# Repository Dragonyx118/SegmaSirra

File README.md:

# 🌿 SegmaSirra — Smart Solar Greenhouse

<p align="center">
<b>Un'ecosistema IoT completo per la gestione, l'irrigazione e il monitoraggio remoto di una serra automatizzata e autosufficiente.</b>
</p>

<br />

---

## 📌 Indice
- [Cos'è SegmaSirra?](#-cosè-segmasirra)
- [Galleria Fotografica](#-galleria-fotografica)
- [Architettura del Sistema](#-architettura-del-sistema)
- [Specifiche Hardware](#-specifiche-hardware)
- [Funzionalità nel Dettaglio](#-funzionalità-nel-dettaglio)
- [Struttura della Repository](#-struttura-della-repository)
- [Guida all'Installazione](#-guida-allinstallazione)
- [1. Firmware (ESP32)](#1-firmware-esp32)
- [2. App Android](#2-app-android)
- [Roadmap & Sviluppi Futuri](#-roadmap--sviluppi-futuri)
- [Licenza](#-licenza)

---

## 🍃 Cos'è SegmaSirra?

**SegmaSirra** è una serra domotica completamente **autosufficiente dal punto di vista energetico**, progettata per ottimizzare la crescita delle piante senza richiedere interventi umani continui.
**SegmaSirra** è una serra domotica completamente **autosufficiente**, progettata per ottimizzare la crescita delle piante senza richiedere interventi umani continui.

Grazie al microcontrollore **ESP32-WROOM-32** e all'alimentazione integrata da pannello solare a 12V, il sistema analizza costantemente i parametri ambientali (temperatura, umidità del suolo e dell'aria, luminosità) ed esegue azioni correttive automatiche. Tutto l'ecosistema è interfacciato in tempo reale con un'app Android dedicata tramite connessione Wi-Fi.

🌐 **Sito del Progetto:** [dragonyx118.github.io/SegmaSirra-Web/](https://dragonyx118.github.io/SegmaSirra-Web/)

---

## 📱 App Android (SegmaIpp)

Il controllo e il monitoraggio remoto della serra avvengono tramite un'applicazione Android sviluppata ad hoc e ospitata in una repository dedicata:

👉 **Repository dell'App:** [**Dragonyx118/SegmaIpp**](https://github.com/Dragonyx118/SegmaIpp)

### Caratteristiche dell'App:
* **Dashboard in tempo reale:** Visualizzazione dei dati di temperatura, umidità ambientale, umidità del terreno e luminosità.
* **Controllo remoto manuale:** Attivazione forzata dell'irrigazione, gestione delle luci notturne ed apertura/chiusura del tetto via Wi-Fi.
* **Notifiche ed avvisi:** Monitoraggio dello stato delle cisterne e della batteria.

---

## 📸 Galleria Fotografica
## 📸 Galleria

<div align="center">
<table>
<tr>
 <td align="center" width="50%">
   <br />
   <b></b>
 </td>
 <td align="center" width="50%">
   <br />
   <b></b>
 </td>
</tr>
<tr>
 <td align="center" width="50%">
   <br />
   <b></b>
 </td>
 <td align="center" width="50%">
   <br />
   <b></b>
 </td>
</tr>
</table>
</div>

---

## ⚡ Architettura del Sistema

```text
              +----------------------------------+
              |     Pannello Solare + Reg.      |
              +-----------------+----------------+
                                |
                                v
                      +------------------+
                      | Batteria AGM 12V |
                      +--------+---------+
                                |
                                v
+--------------------------------+--------------------------------+
|                       Modulo ESP32-WROOM-32                      |
|                                                                 |
|  [Sensori Clima & Luce]  --->  Elaborazione Data  --->  [Wi-Fi] |
+-------+------------------------+------------------------+-------+
       |                        |                        |
       v                        v                        v
+---------------+        +---------------+        +---------------+
|   Attuatori   |        | Servomotori   |        |  App Android  |
| 2x Ventole    |        | Apertura      |        | Monitoraggio  |
| 2x Pompe 12V  |        | Tetto         |        |  & Comandi    |
| Luci Notturne |        +---------------+        +---------------+

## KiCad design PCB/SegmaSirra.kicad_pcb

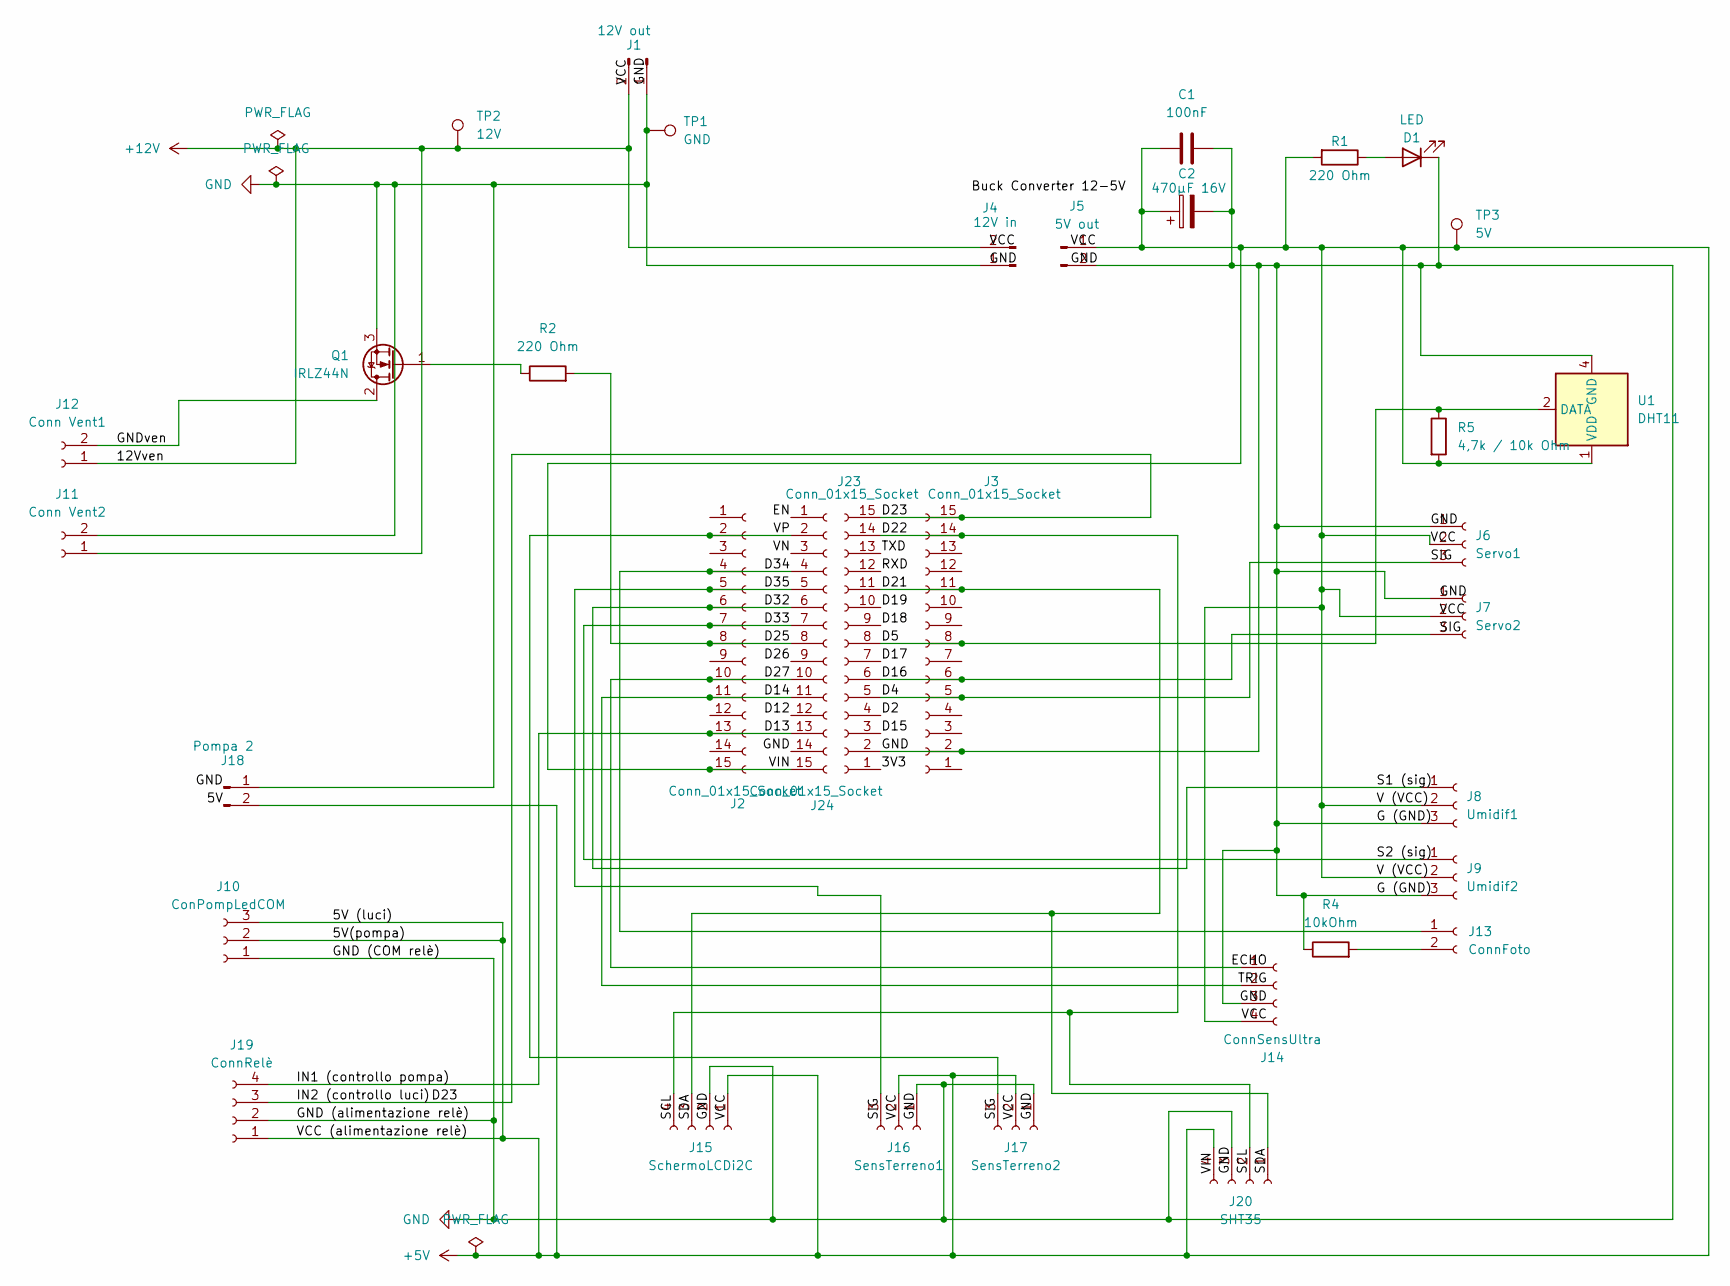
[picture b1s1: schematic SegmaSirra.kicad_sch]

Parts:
C1: 100nF; C_Disc_D5.0mm_W2.5mm_P5.00mm
C2: 470µF 16V; CP_Radial_D8.0mm_P3.50mm
D1: LED; LED_D5.0mm
J1: 12V out; TerminalBlock_Phoenix_MKDS-1,5-2_1x02_P5.00mm_Horizontal
J2, J3, J23, J24: Conn_01x15_Socket; PinSocket_1x15_P2.54mm_Vertical
J4: 12V in; TerminalBlock_Phoenix_MKDS-1,5-2_1x02_P5.00mm_Horizontal
J5: 5V out; TerminalBlock_Phoenix_MKDS-1,5-2_1x02_P5.00mm_Horizontal
J6: Servo1; PinSocket_1x03_P2.54mm_Vertical
J7: Servo2; PinSocket_1x03_P2.54mm_Vertical
J8: Umidif1; PinSocket_1x03_P2.54mm_Vertical
J9: Umidif2; PinSocket_1x03_P2.54mm_Vertical
J10: ConPompLedCOM; TerminalBlock_Phoenix_MKDS-1,5-3_1x03_P5.00mm_Horizontal
J11: Conn Vent2; JST_PH_B2B-PH-K_1x02_P2.00mm_Vertical
J12: Conn Vent1; JST_PH_B2B-PH-K_1x02_P2.00mm_Vertical
J13: ConnFoto; PinSocket_1x02_P2.54mm_Vertical
J14: ConnSensUltra; PinSocket_1x04_P2.54mm_Vertical
J15: SchermoLCDi2C; PinSocket_1x04_P2.54mm_Vertical
J16: SensTerreno1; PinSocket_1x03_P2.54mm_Vertical
J17: SensTerreno2; PinSocket_1x03_P2.54mm_Vertical
J18: Pompa 2; TerminalBlock_Phoenix_MKDS-1,5-2_1x02_P5.00mm_Horizontal
J19: ConnRelè; TerminalBlock_Phoenix_MKDS-1,5-4_1x04_P5.00mm_Horizontal
J20: SHT35; PinSocket_1x04_P2.54mm_Vertical
Q1: IRLZ44N; TO-220-3_Vertical
R1, R2: 220 Ohm; R_Axial_DIN0207_L6.3mm_D2.5mm_P7.62mm_Horizontal
R4: 10kOhm; R_Axial_DIN0207_L6.3mm_D2.5mm_P7.62mm_Horizontal
R5: 4,7k / 10k Ohm; R_Axial_DIN0207_L6.3mm_D2.5mm_P7.62mm_Horizontal
TP1: GND; TestPoint_Pad_D1.5mm
TP2: 12V; TestPoint_Pad_D1.5mm
TP3: 5V; TestPoint_Pad_D1.5mm
U1: DHT11; Aosong_DHT11_5.5x12.0_P2.54mm

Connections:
+5V: C1.1, C2.1, J2.15, J5.1, J6.2, J7.2, J8.2, J9.2, J10.2, J10.3, J14.4, J15.1, J16.2, J17.2, J18.2, J19.1, J20.4, J24.15, R1.2, R5.2, TP3.1, U1.1 (VDD)
+12V: J1.2, J4.2, J11.1, J12.1, TP2.1
/3V3: J23.1
/D2: J23.4
/D4: J3.5, J6.3, J23.5
/D5: J3.8, J23.8, R5.1, U1.2 (DATA)
/D12: J24.12
/D13: J2.13, J19.4, J24.13
/D14: J2.11, J14.2, J24.11
/D15: J23.3
/D16: J3.6, J7.3, J23.6
/D17: J23.7
/D18: J23.9
/D19: J23.10
/D21: J3.11, J15.3, J20.1, J23.11
/D22: J3.14, J15.4, J20.2, J23.14
/D23: J3.15, J19.3, J23.15
/D25: J2.8, J24.8, R2.2
/D26: J24.9
/D27: J2.10, J14.1, J24.10
/D32: J2.6, J8.1, J24.6
/D33: J2.7, J9.1, J24.7
/D34: J2.4, J13.1, J24.4
/D35: J2.5, J16.3, J24.5
/EN: J24.1
/GNDven: J12.2, Q1.2 (D)
/RXD: J23.12
/TXD: J23.13
/VN: J24.3
/VP: J2.2, J17.3, J24.2
GND: C1.2, C2.2, D1.1 (K), J1.1, J3.2, J4.1, J5.2, J6.1, J7.1, J8.3, J9.3, J10.1, J11.2, J14.3, J15.2, J16.1, J17.1, J18.1, J19.2, J20.3, J23.2, J24.14, Q1.3 (S), R4.1, TP1.1, U1.4 (GND)
unnamed: D1.2 (A), R1.1
unnamed: J13.2, R4.2
unnamed: Q1.1 (G), R2.1

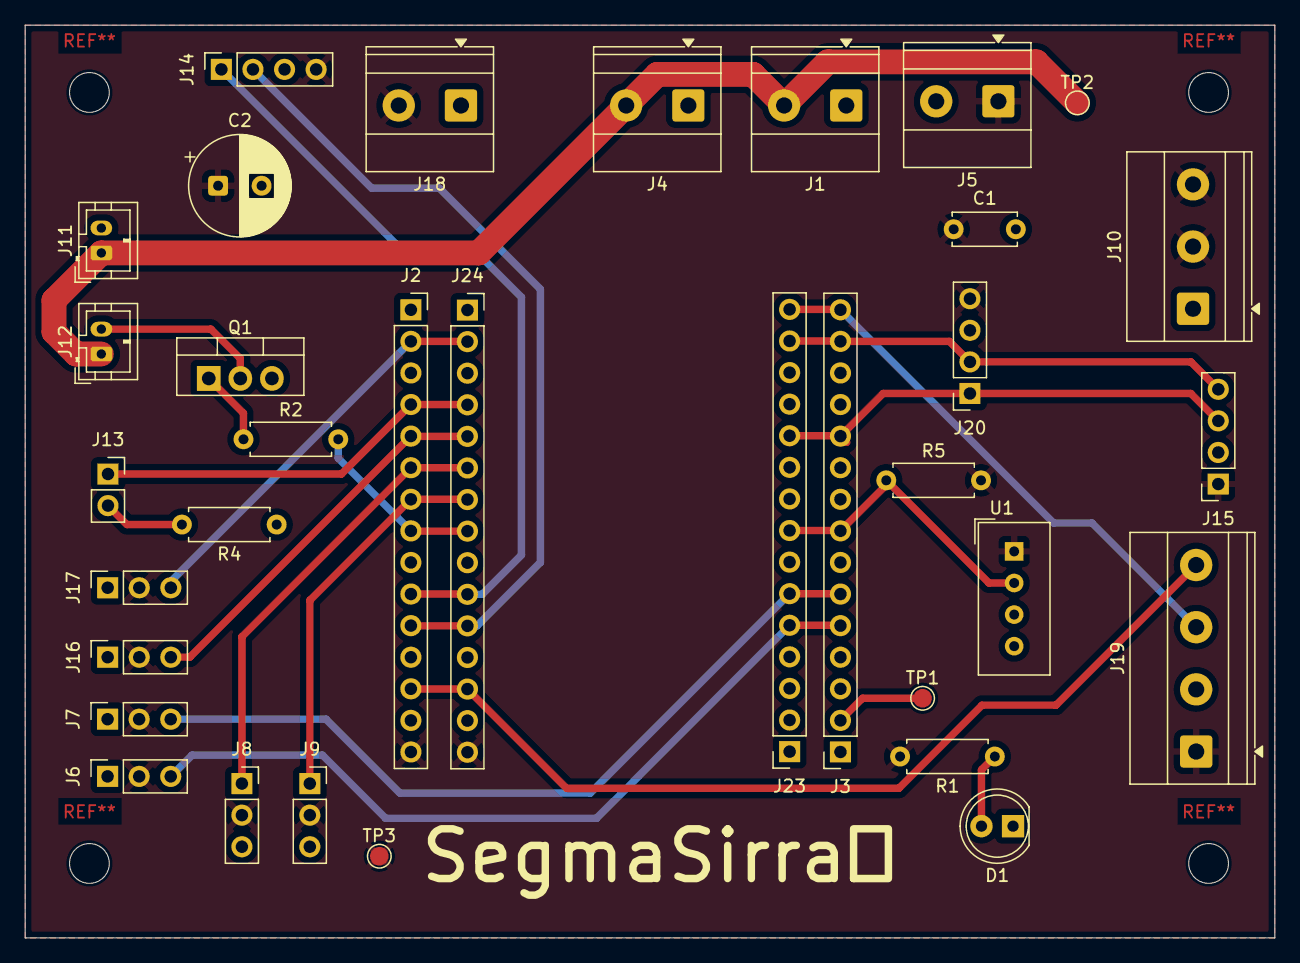
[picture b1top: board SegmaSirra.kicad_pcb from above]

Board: 2 copper layers, 100.5 x 73.4 mm, 34 parts (0 on the bottom side), 22 nets.

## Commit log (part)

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2026-04-23 primo commit
2026-06-10 Create LICENSE

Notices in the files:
README.md:
MIT License
